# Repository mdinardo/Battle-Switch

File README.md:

Battle-Switch
=============

High power relay board for robotics applications.

Compatible with hobby aircraft RC receivers, or any other device that can output the same type of signal pulses.

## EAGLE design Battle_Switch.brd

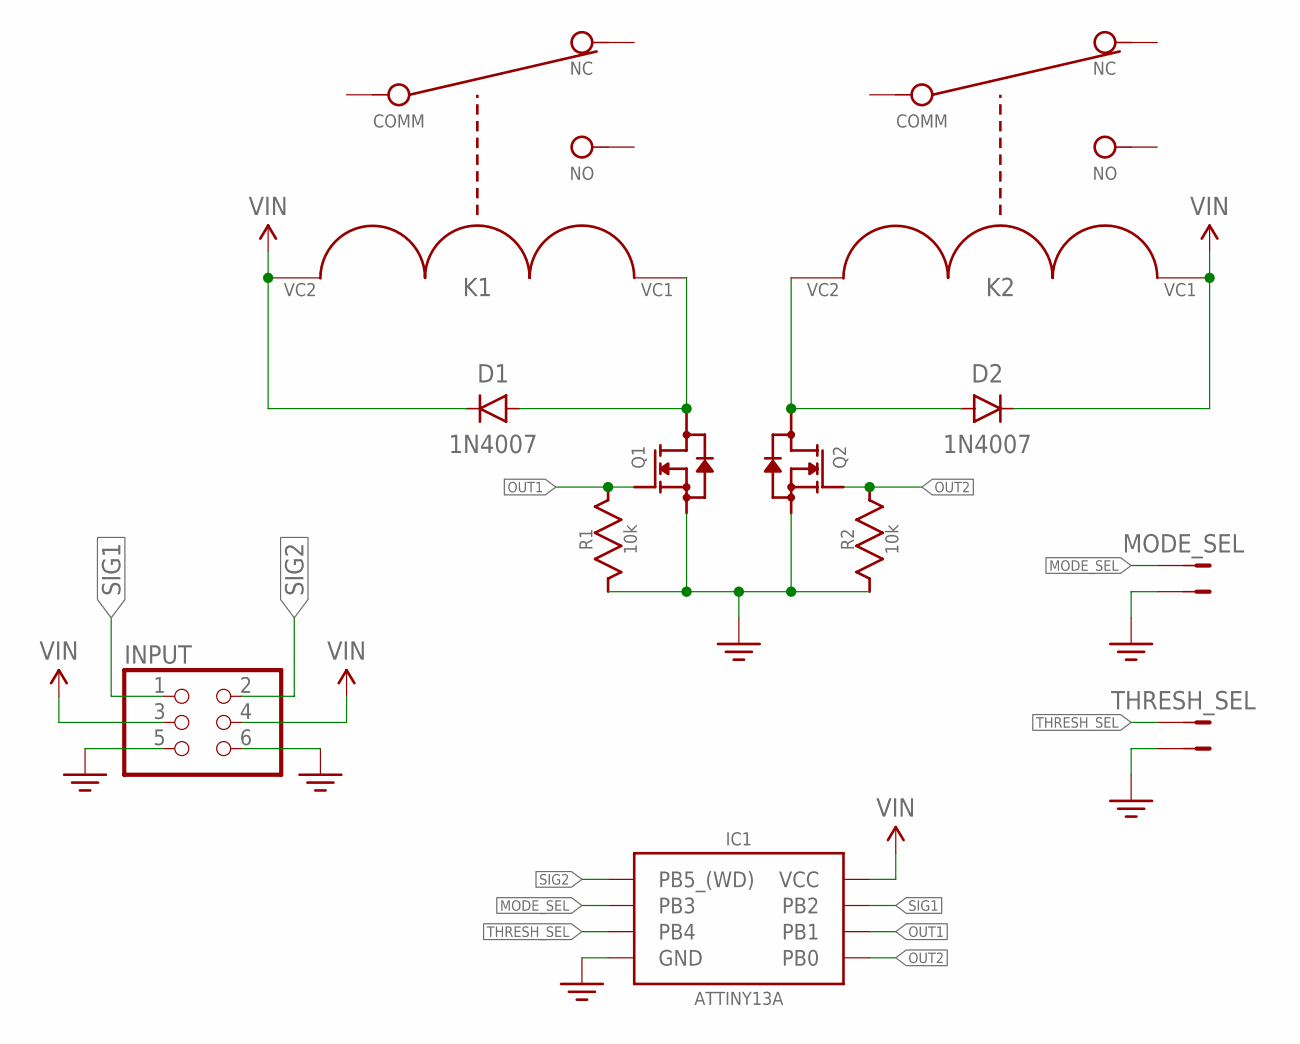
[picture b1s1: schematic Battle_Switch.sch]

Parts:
D1, D2: 1N4007; DIODE-1N4001
IC1: ATTINY13A; 8-PDIP
INPUT: PINHD-2X3; 2X03
K1, K2: AZ2100-1C-5DE; AZ2100
MODE_SEL: JUMPER-PTH-2-NO; PTH-JUMPER-2-NO
Q1, Q2: BS170; TO-92-AMMO
R1, R2: 10k; 0411/15
THRESH_SEL: JUMPER-PTH-2-NO; PTH-JUMPER-2-NO

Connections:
GND: IC1.P$4 (GND), INPUT.5, INPUT.6, MODE_SEL.P$2 (2), Q1.1 (SOURCE), Q2.1 (SOURCE), R1.2, R2.1, THRESH_SEL.P$2 (2)
MODE_SEL: IC1.P$2 (PB3), MODE_SEL.P$1 (1)
unnamed: D1.A, K1.VC1, Q1.3 (DRAIN)
unnamed: D2.A, K2.VC2, Q2.3 (DRAIN)
OUT1: IC1.P$6 (PB1), Q1.2 (GATE), R1.1
OUT2: IC1.P$5 (PB0), Q2.2 (GATE), R2.2
SIG1: IC1.P$7 (PB2), INPUT.1
SIG2: IC1.P$1 (PB5_(WD)), INPUT.2
THRESH_SEL: IC1.P$3 (PB4), THRESH_SEL.P$1 (1)
VIN: D1.C, D2.C, IC1.P$8 (VCC), INPUT.3, INPUT.4, K1.VC2, K2.VC1

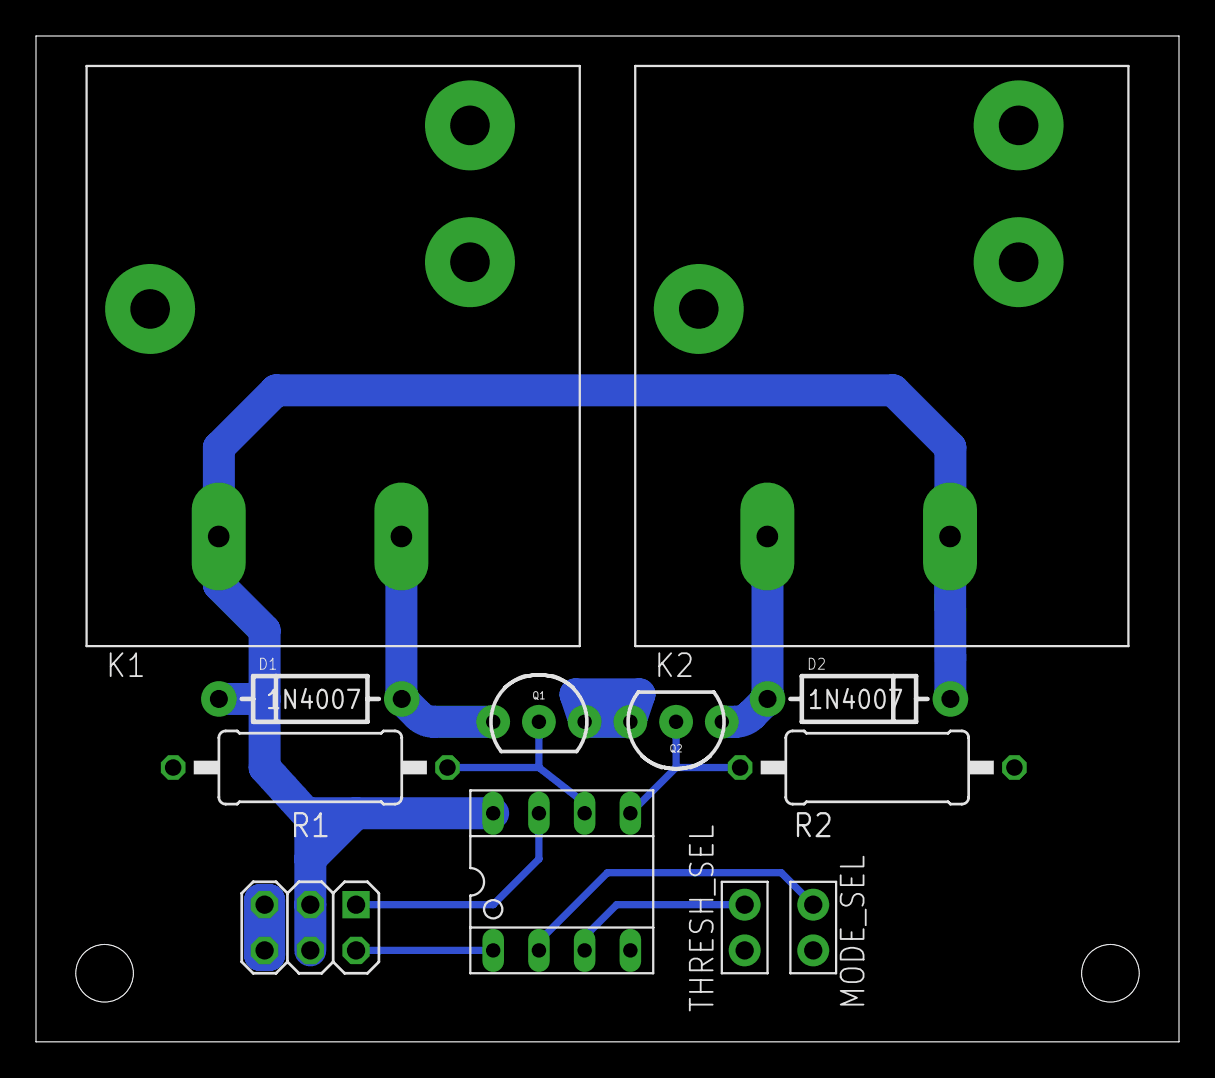
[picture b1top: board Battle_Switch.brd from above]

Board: 2 copper layers, 63.5 x 55.9 mm, 12 parts (0 on the bottom side), 10 nets.

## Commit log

2014-11-25 Added Attiny13A datasheet
2014-11-25 Added mode and threshold select jumpers.
2014-11-26 removed project file (.epf) from git
2014-12-02 Completed board layout. Ready for copper ground pour.
2014-12-08 Added a design rule check, adapted from OSH Park's 2 layer DRU.
2014-12-09 Revision A layout complete. Ready for silkscreen additions.
